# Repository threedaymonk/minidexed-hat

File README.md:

# MiniDexed Hat for Raspberry Pi

This aims to make the construction of a
[MiniDexed](https://github.com/probonopd/MiniDexed) a little easier.

Features:

- On-board step-down converter to run from a typical 12V wall-wart power supply
  to sidestep the exacting USB-C requirements of the Raspberry Pi 4
- Direct mounting for a PCM5102A audio module, with output routed to headers
- Headers for connecting peripherals:
  - 8 pins for a 1602 display (using [this backpack
    board](https://po-ru.com/pcb/1602))
  - I2C for an OLED display
  - Left and right line out
  - Serial MIDI for a [3.3V MIDI interface](https://po-ru.com/pcb/midi)
  - KY-040 encoder module

Revision 1 does not include debouncing capacitors for the encoder. I intend to
make my own encoder boards with better debouncing.

The PCB dimensions are based on [Seth Hillbrand's
template](https://github.com/sethhillbrand/kicad_templates) for a Raspberry Pi
hat.

With an appropriate display, this board should also work with
[mt32-pi](https://github.com/dwhinham/mt32-pi), but I have not tested it.

## Warning

Set the voltage on the converter **before** soldering the audio interface in
place or installing the hat on the Pi. I recommend around 5.2V.

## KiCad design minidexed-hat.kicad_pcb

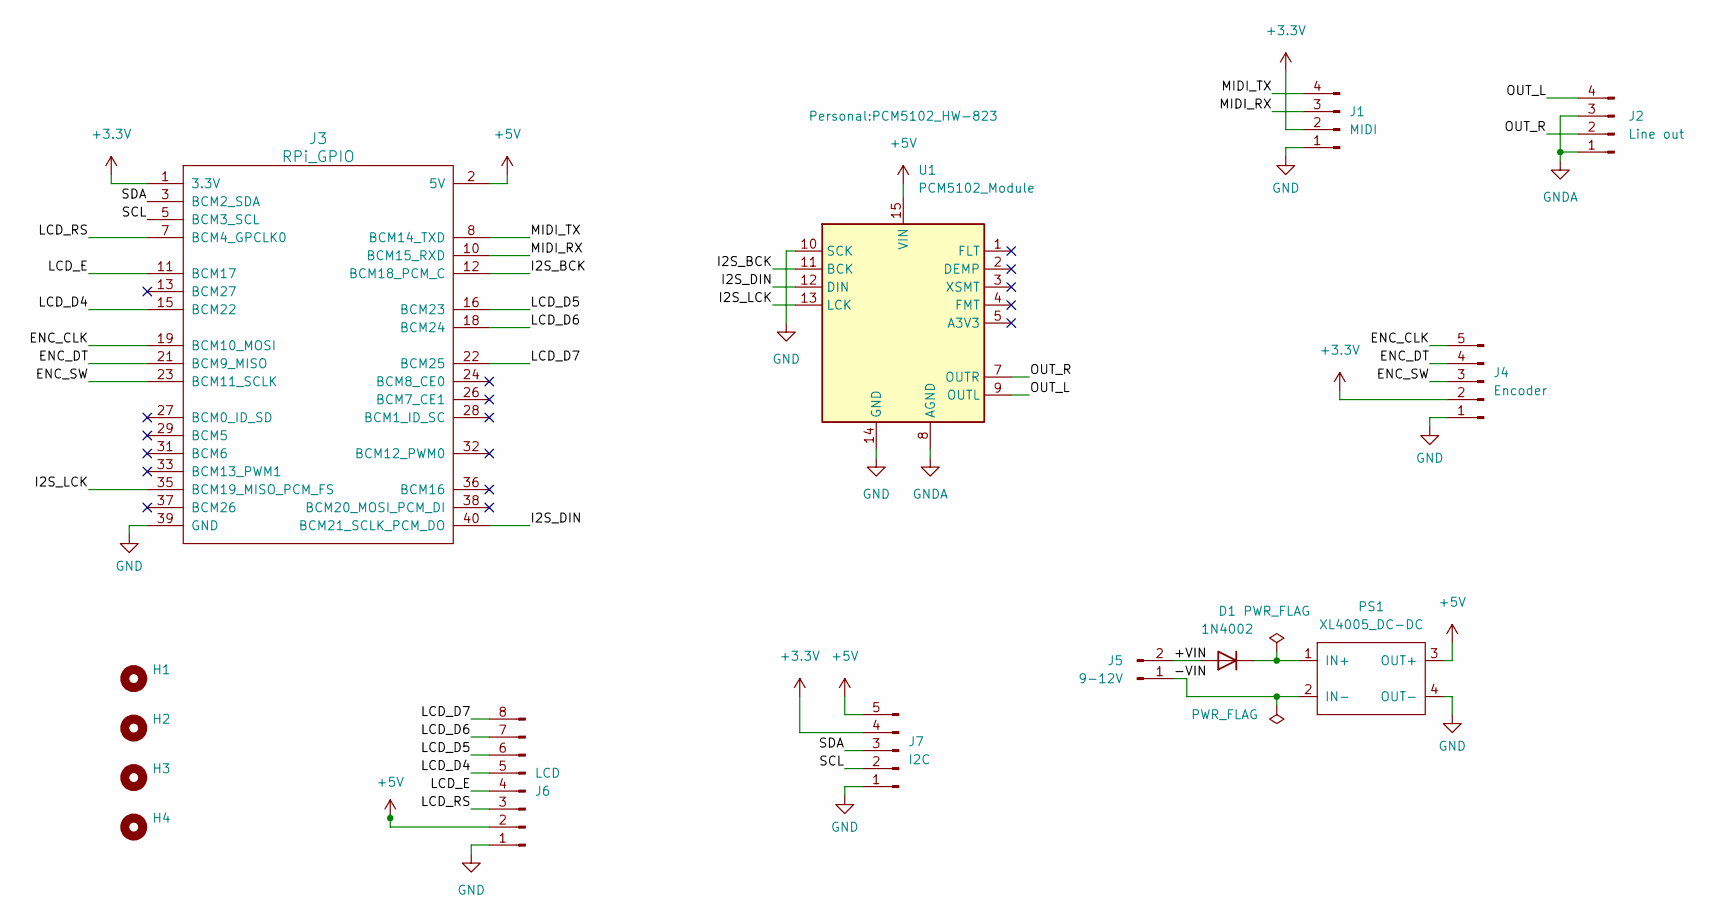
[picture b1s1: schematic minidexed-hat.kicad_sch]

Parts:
D1: 1N4002; D_DO-41_SOD81_P10.16mm_Horizontal
H1, H2, H3, H4: RPi_Hat_Mounting_Hole
J1: MIDI; PinHeader_1x04_P2.54mm_Vertical
J2: Line out; PinHeader_1x04_P2.54mm_Vertical
J3: RPi_GPIO; PinSocket_2x20_P2.54mm_Vertical
J4: Encoder; PinHeader_1x05_P2.54mm_Vertical
J5: 9-12V; PinHeader_1x02_P2.54mm_Vertical
J6: LCD; PinHeader_1x08_P2.54mm_Vertical
J7: I2C; PinHeader_1x05_P2.54mm_Vertical
PS1: XL4005_DC-DC
U1: PCM5102_Module; PCM5102_HW-823

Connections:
+3.3V: J1.2, J3.1 (3.3V), J3.17 (3.3V), J4.2, J7.4
+5V: J3.2 (5V), J3.4 (5V), J6.2, J7.5, PS1.3 (OUT+), U1.15 (VIN)
/+VIN: D1.2 (A), J5.2
/-VIN: J5.1, PS1.2 (IN-)
/ENC_CLK: J3.19 (BCM10_MOSI), J4.5
/ENC_DT: J3.21 (BCM9_MISO), J4.4
/ENC_SW: J3.23 (BCM11_SCLK), J4.3
/I2S_BCK: J3.12 (BCM18_PCM_C), U1.11 (BCK)
/I2S_DIN: J3.40 (BCM21_SCLK_PCM_DO), U1.12 (DIN)
/I2S_LCK: J3.35 (BCM19_MISO_PCM_FS), U1.13 (LCK)
/LCD_D4: J3.15 (BCM22), J6.5
/LCD_D5: J3.16 (BCM23), J6.6
/LCD_D6: J3.18 (BCM24), J6.7
/LCD_D7: J3.22 (BCM25), J6.8
/LCD_E: J3.11 (BCM17), J6.4
/LCD_RS: J3.7 (BCM4_GPCLK0), J6.3
/MIDI_RX: J1.3, J3.10 (BCM15_RXD)
/MIDI_TX: J1.4, J3.8 (BCM14_TXD)
/OUT_L: J2.4, U1.9 (OUTL)
/OUT_R: J2.2, U1.7 (OUTR)
/SCL: J3.5 (BCM3_SCL), J7.2
/SDA: J3.3 (BCM2_SDA), J7.3
GND: J1.1, J3.6 (GND), J3.9 (GND), J3.14 (GND), J3.20 (GND), J3.25 (GND), J3.30 (GND), J3.34 (GND), J3.39 (GND), J4.1, J6.1, J7.1, PS1.4 (OUT-), U1.10 (SCK), U1.14 (GND)
GNDA: J2.1, J2.3, U1.6 (AGND), U1.8 (AGND)
unnamed: D1.1 (K), PS1.1 (IN+)

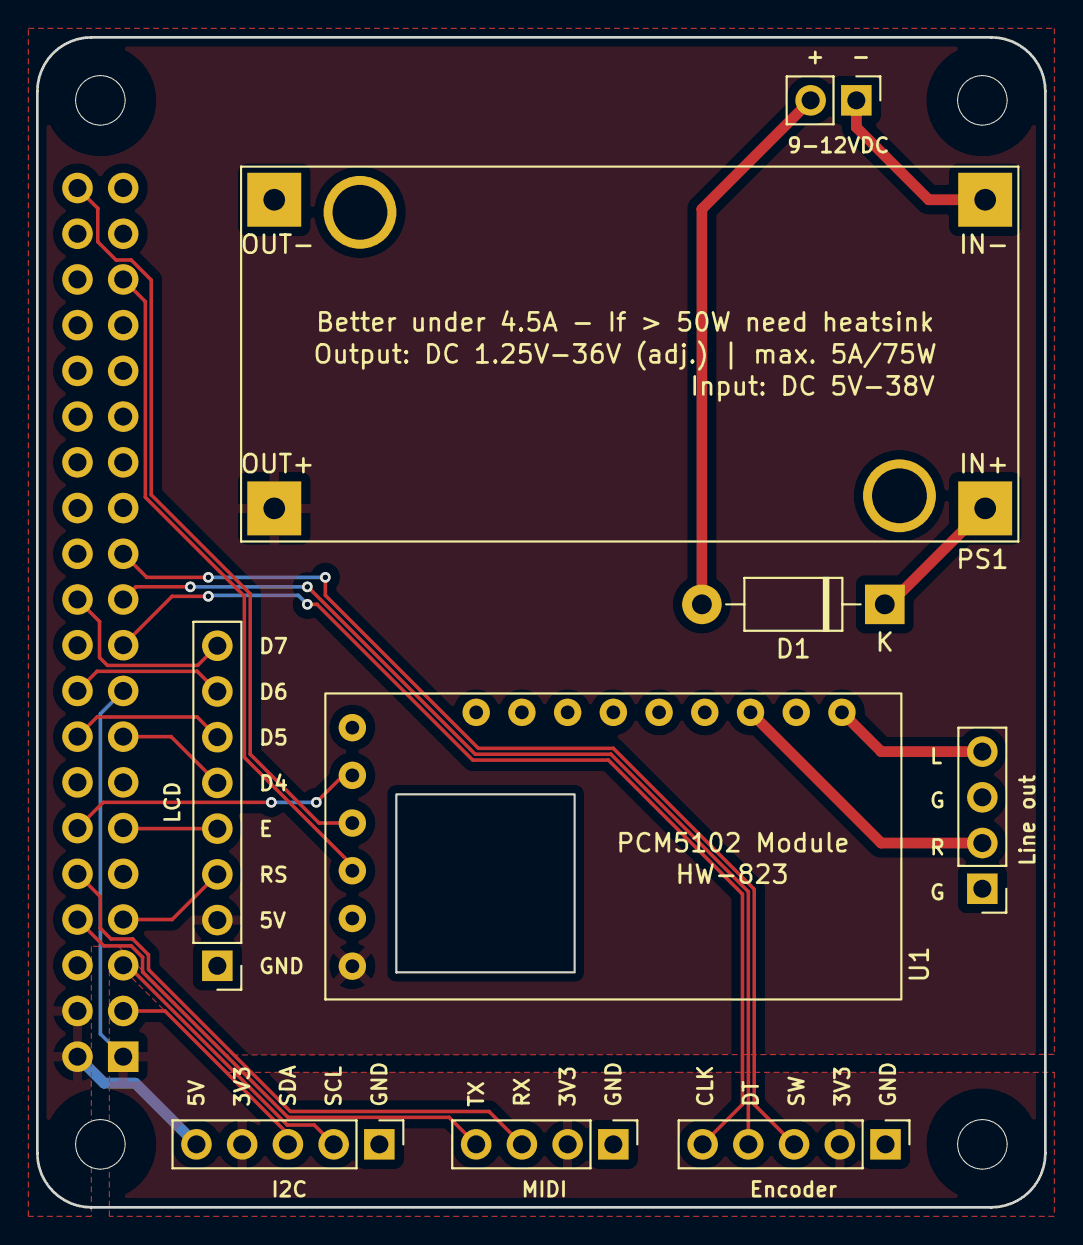
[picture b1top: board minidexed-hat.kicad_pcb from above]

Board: 2 copper layers, 56.0 x 65.0 mm, 14 parts (1 on the bottom side), 25 nets.

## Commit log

2022-10-13 Initial empty commit
2022-10-13 Create new repo for my template
    This is based on https://github.com/sethhillbrand/kicad_templates
    updated to Kicad 6 and using A4 paper.
2022-10-13 Import basic PCB shape
    From https://github.com/devbisme/RPi_Hat_Template
2022-10-30 Complete with MIDI and connectors off-board
2022-10-30 Save rounded track configuration
2022-10-30 Tweak tracks to preserve spacing when rounding
2022-10-30 Add text
2022-10-30 Add placeholder for order number
2022-10-30 Ignore JLC files
2022-10-30 Add documentation
2022-10-30 Add note about mt32-pi
2022-10-30 Add photo to README
2022-10-30 Add warning about power
